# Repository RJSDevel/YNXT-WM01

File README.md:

# YNXT-WM01
Zigbee Water meter device for YF-S402B counter

The device was created for counting flow and volume passed through kitchen water filter, and it has three independent count channels for measurement, also has buzzer for remind to change filters and extranal load MOSFET for e.g unleak valve enable 
Zigbee2Mqtt supported by [External convector](/YNXT-WM-01.js)

## Z2M and HA Views

## Scheme

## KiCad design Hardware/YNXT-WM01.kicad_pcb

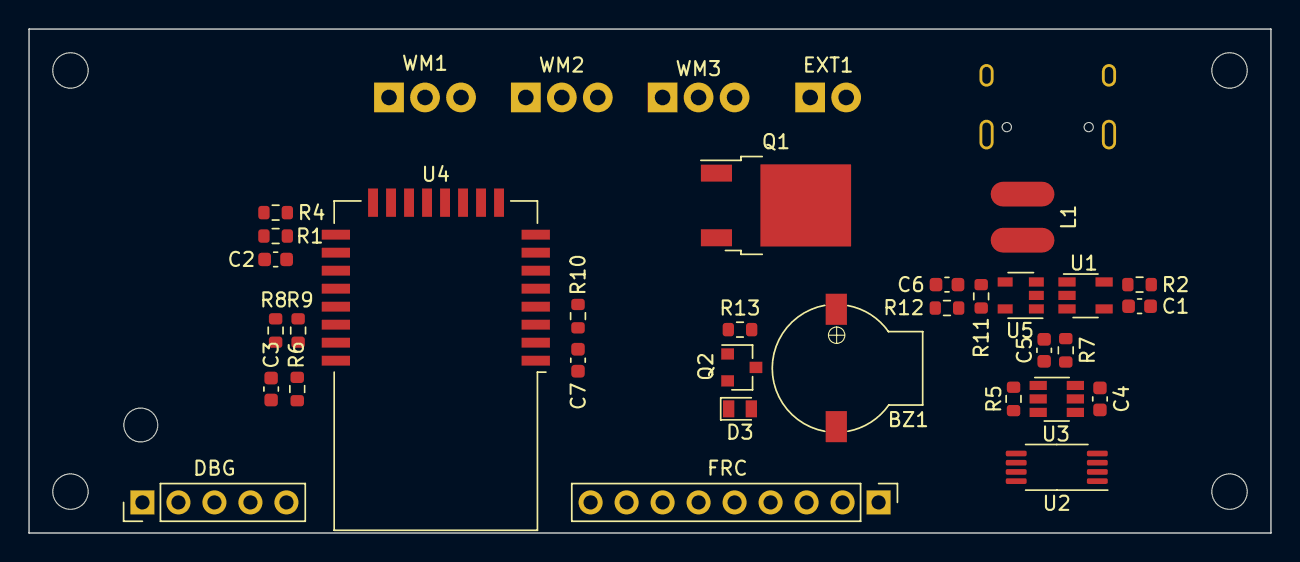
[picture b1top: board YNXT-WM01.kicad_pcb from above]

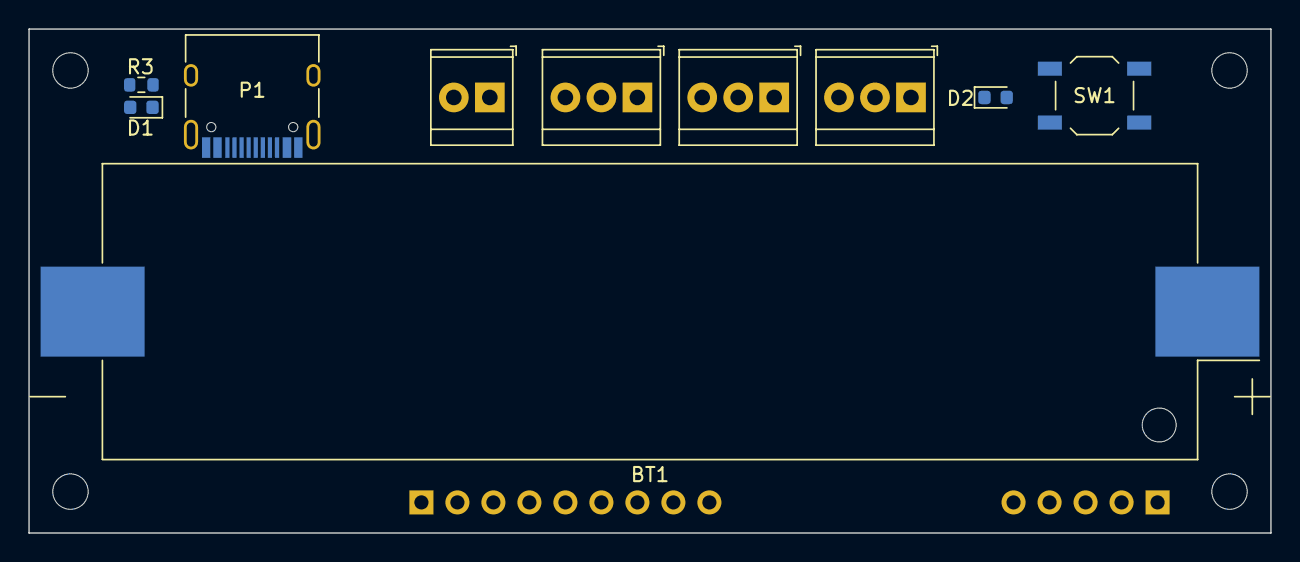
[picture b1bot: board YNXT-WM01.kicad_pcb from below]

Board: 2 copper layers, 87.6 x 35.6 mm, 45 parts (10 on the bottom side), 41 nets, no tracks yet.

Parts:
BT1: BAT; BatteryHolder_Blossom_1042_1x18650
BZ1: Buzzer; MLT-9032
C1: 1uF; C_0603_1608Metric
C2, C3, C4, C7: 100nF; C_0603_1608Metric
C5: 4.7uF; C_0603_1608Metric
C6: 10uF; C_0603_1608Metric
D1, D2: LED; LED_0603_1608Metric
D3: D; D_MicroMELF
DBG: DEBUG; PinHeader_1x05_P2.54mm_Vertical
EXT1: External Load; TerminalBlock_TE_282834-2_1x02_P2.54mm_Horizontal
FRC: Free; PinHeader_1x09_P2.54mm_Vertical
H1, H2, H3, H4: MountingHole; MountingHole_2.5mm
L1: 2.2uH; CD43
P1: USB_C_Plug; USB_C_Receptacle_HRO_TYPE-C-31-M-12
Q1: Q_NMOS_DGS; TO-252-2
Q2: Q_NPN_BCE; SOT-23
R1, R11: 10k; R_0603_1608Metric
R2: 1.65k; R_0603_1608Metric
R3, R4: 500; R_0603_1608Metric
R5, R6, R10: 1k; R_0603_1608Metric
R7: 100; R_0603_1608Metric
R8, R9: ???; R_0603_1608Metric
R12: 45.3k; R_0603_1608Metric
R13: 470; R_0603_1608Metric
SW1: SW_Push; SW_SPST_TL3342
U1: LTC4054ES5-4.2; TSOT-23-5
U2: FS8205A; TSSOP-8_4.4x3mm_P0.65mm
U3: DW01A; TSOT-23-6
U4: E18-MS1-PCB
U5: STI3408B; SOT-23-5
WM1: First; TerminalBlock_TE_282834-3_1x03_P2.54mm_Horizontal
WM2: Second; TerminalBlock_TE_282834-3_1x03_P2.54mm_Horizontal
WM3: Third; TerminalBlock_TE_282834-3_1x03_P2.54mm_Horizontal

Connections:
+3V3: C6.1, C7.1, DBG.5, L1.2, R1.1, R10.2, R12.2, U4.2, WM1.1, WM2.1, WM3.1
+5V: C1.2, P1.A4, P1.A9, P1.B4, P1.B9, R3.1, U1.4
+BATT: BT1.1, BZ1.1, C5.1, D3.1, R7.2, R8.2, U1.3, U5.1, U5.4
/BAT_ADC: R8.1, R9.2, U4.23
/BUZZER: R13.2, U4.6
/CAPTURE0: U4.21, WM1.2
/CAPTURE1: U4.20, WM2.2
/CAPTURE2: U4.19, WM3.2
/DC: DBG.3, R10.1, U4.3
/DD: DBG.4, U4.4
/EXT_LOAD: Q1.1, U4.22
/KEY: C2.1, SW1.2, U4.18
/LED: R4.2, U4.17
/P0.7: FRC.9, U4.16
/P1.0: FRC.8, U4.15
/P1.1: FRC.7, U4.14
/P1.2: FRC.6, U4.13
/P1.3: FRC.5, U4.12
/P1.4: FRC.4, U4.11
/P1.5: FRC.3, U4.10
/P1.6: FRC.2, U4.7
/P2.0: FRC.1, U4.5
/RESET: DBG.2, R6.2
GND: C1.1, C2.2, C3.1, C5.2, C6.2, C7.2, D2.1, DBG.1, EXT1.2, P1.A1, P1.A12, P1.B1, P1.B12, P1.S1, Q1.3, Q2.3, R2.1, R9.1, R11.1, U1.2, U2.6, U2.7, U4.1, U5.2, WM1.3, WM2.3, WM3.3
unnamed: BT1.2, C4.2, R5.1, U2.2, U2.3, U3.6
unnamed: BZ1.2, D3.2, Q2.2
unnamed: C3.2, R6.1, U4.24
unnamed: C4.1, R7.1, U3.5
unnamed: D1.1, U1.1
unnamed: D1.2, R3.2
unnamed: D2.2, R4.1
unnamed: EXT1.1, Q1.2
unnamed: L1.1, U5.3
unnamed: Q2.1, R13.1
unnamed: R1.2, SW1.1
unnamed: R2.2, U1.5
unnamed: R5.2, U3.2
unnamed: R11.2, R12.1, U5.5
unnamed: U2.1, U2.8
unnamed: U2.4, U3.1
unnamed: U2.5, U3.3

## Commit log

2022-09-03 Add z2m convector
2022-09-04 Fix Firmware project compile issues, fix software save NVM states and enter to sleep mode
2022-09-05 Add reset volume, update enable device
2022-09-07 Remade count impulse to liters, fix disapperearance of volume
2022-09-09 Add reset volume for each channel, edit scheme elements values
2022-09-09 Add images of scheme
